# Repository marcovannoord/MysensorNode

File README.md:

# MysensorNode
A MySensor node that uses an NTF24l01+ wireless unit to connect to the gateway. We use an Arduino Nano. In this repository you'll find the files i used to design the PCB (KiCad). Unless you're planning to produce your own boards, you don't need those files. 

If you use this board, it means you've connected your Arduino Nano to your NRF24L01+. Also the pins of the Nano are broken out (at the side of the Nano), so you can easily solder wires to them or even use some fancy headers to connect your creations. 

# Why use an arduino Nano instead of the Pro mini? 
Okay, this is a tradeoff between usability and energy-consumption. The pro mini is way better in terms of size and energy-consumption - it doesn't have the usb-controller - but is a lot harder for beginners to program, and using an FTDI-cable might be a bit scary for beginning users. 

If you wanna save energy , just cut the powertraces for the usb-serial chip. If you're feeling fancy, make a header so you can reconnect the usb-serial. Or you can just program it using the ICSP header using a programmer :) 

# Getting started: getting mysensors working
After you made yourself familiar with the mySensors system https://www.mysensors.org , you figured you need a gateway and of course some nodes to which you connect sensors.

## Warning: Install the library from the MySensors.zip i attached in this repo.

1. Solder female headers on the PCB, exactly where the Arduino Nano is supposed to be and also where the NRF24L01+ should connect. This way you can always remove the nano for testing purposes.
2. Connect the two pins next to "Nano3v3 to NRF" to each other, which will supply the wireless chip with some juice.
3. solder a 47uF electrolythic condensator to C1. Make sure that the "-" of the ElCo faces the same side as the "-" on the PCB.
4. Plug in the Arduino Nano (USB connector should be slightly sticking out) and the NRF24L01+(not sticking out).
5. Plug in the USB, and upload the "SerialGateway" sketch from the MySensors arduino library (https://www.mysensors.org/build/serial_gateway). 
6. Make any of the sensors, for example https://www.mysensors.org/build/binary . 
7. Connect the serial gateway to a Controller (i advice https://www.mysensors.org/controller/mynodesnet or Domoticz) and you're ready to receive data! (p.s. there's a controller in the greenhouse @ RDM already available, connect to DoosWifi and connect to Raspberrypiarjen.local )

After powering on your wireless node, it will search for an active controller in the network, which it will ask a unique device id; it will store that internally in its EEPROM. It will be saved even after losing power. Now you can send data to the controller. Using default settings, you can send/receive approximately 200 messages per second.

# FAQ:

Q: i get an error compiling the system can't find MySensors.h

A: in your sketch, change the reference from mysensors.h to MySensor.h (so remove the "s").

# More Info:
See the Wiki <https://github.com/marcovannoord/MysensorNode/wiki>

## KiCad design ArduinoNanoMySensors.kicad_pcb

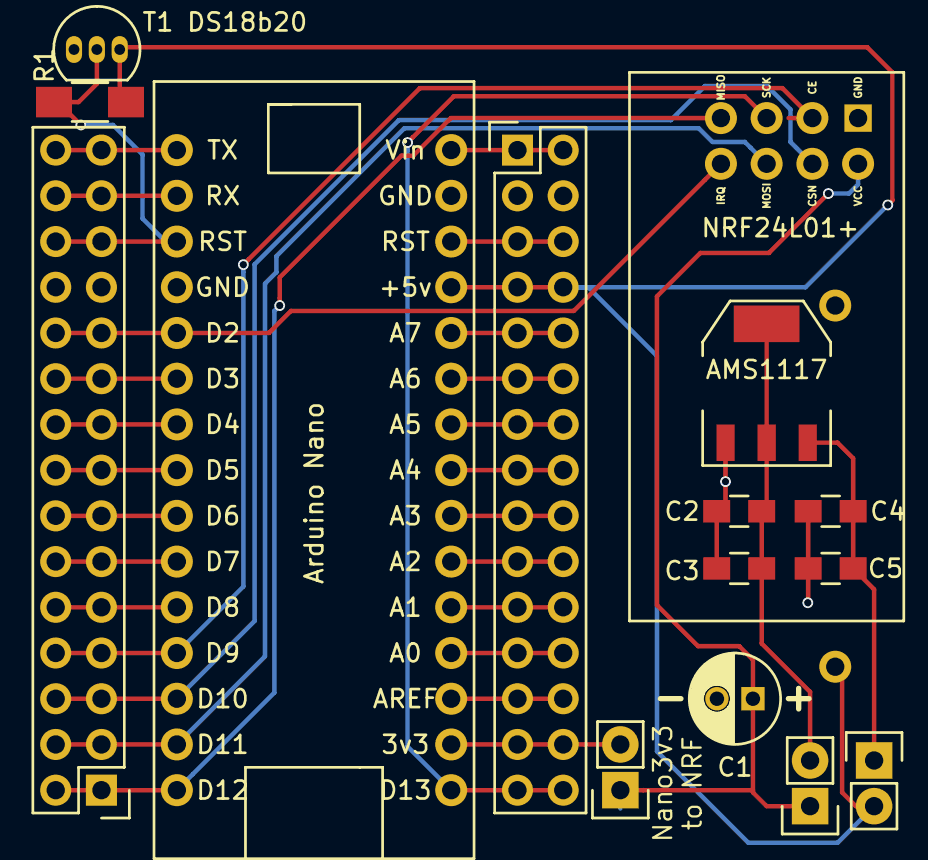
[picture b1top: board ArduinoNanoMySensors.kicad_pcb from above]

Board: 2 copper layers, 16 parts (1 on the bottom side), 32 nets.

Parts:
AMS1117: AMS1117; SOT-223
Arduino Nano: ArduinoNano
BT1: Battery; CR3032Holder
C1: 100u; C_Radial_D5_L11_P2
C2, C5: 10u; C_0805_HandSoldering
C3, C4: 0.1u; C_0805_HandSoldering
JP1, JP2, JP3: JUMPER; Pin_Header_Straight_1x02
NRF24L01+: NRF24L01+
P1, P2: CONN_02X15; Pin_Header_Straight_2x15
R1: 4K7; R_1206_HandSoldering
T1 DS18b20: DS18B20; TO-92_Inline_Narrow_Oval

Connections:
+3V3: C1.1, JP1.1, JP3.1, NRF24L01+.8
GND: AMS1117.1, Arduino Nano.4, Arduino Nano.29, BT1.2, C1.2, C2.2, C3.2, C4.2, C5.2, NRF24L01+.1, P1.23, P1.24, P2.3, P2.4, T1 DS18b20.1
unnamed: Arduino Nano.27, BT1.1, JP2.2, P2.7, P2.8, R1.1, T1 DS18b20.3
unnamed: AMS1117.2, C2.1, C3.1, JP1.2
unnamed: AMS1117.3, C4.1, C5.1, JP2.1
unnamed: Arduino Nano.17, JP3.2, P2.27, P2.28
unnamed: Arduino Nano.15, NRF24L01+.4, P1.1, P1.2
unnamed: Arduino Nano.14, NRF24L01+.6, P1.3, P1.4
unnamed: Arduino Nano.13, NRF24L01+.7, P1.5, P1.6
unnamed: Arduino Nano.12, NRF24L01+.2, P1.7, P1.8
unnamed: Arduino Nano.11, P1.9, P1.10
unnamed: Arduino Nano.10, P1.11, P1.12
unnamed: Arduino Nano.9, P1.13, P1.14
unnamed: Arduino Nano.8, P1.15, P1.16
unnamed: Arduino Nano.7, P1.17, P1.18
unnamed: Arduino Nano.6, P1.19, P1.20
unnamed: Arduino Nano.5, NRF24L01+.5, P1.21, P1.22
unnamed: Arduino Nano.3, P1.25, P1.26, R1.2, T1 DS18b20.2
unnamed: Arduino Nano.2, P1.27, P1.28
unnamed: Arduino Nano.1, P1.29, P1.30
unnamed: Arduino Nano.30, P2.1, P2.2
unnamed: Arduino Nano.28, P2.5, P2.6
unnamed: Arduino Nano.26, P2.9, P2.10
unnamed: Arduino Nano.25, P2.11, P2.12
unnamed: Arduino Nano.24, P2.13, P2.14
unnamed: Arduino Nano.23, P2.15, P2.16
unnamed: Arduino Nano.22, P2.17, P2.18
unnamed: Arduino Nano.21, P2.19, P2.20
unnamed: Arduino Nano.20, P2.21, P2.22
unnamed: Arduino Nano.19, P2.23, P2.24
unnamed: Arduino Nano.18, P2.25, P2.26
unnamed: Arduino Nano.16, NRF24L01+.3, P2.29, P2.30

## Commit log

2016-07-23 Moving everything to Git, everything is now open-source
2016-07-23 Made v0.2 with the following changes:
    - plus en min op batterij x
    -batterijpins dikker x
    -nanopins dikker x
    -nrf pins dikker x
    -polariteit duidelijk bij C1x
    - naamgeving componenten x
2016-09-28 Update README.md
    Wrote a Getting STarted part
2016-10-12 added working library
2016-10-12 updated hole sizes
2016-10-12 Added Hello World sketch to test the node
2016-10-12 Added powerpoint sheets and an image how to connect battery power
2016-10-12 Did some cleaning up
2016-10-20 small bug in NRF mask
